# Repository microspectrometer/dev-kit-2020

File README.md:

Welcome to Chromation's dev-kit resources!

# How to read this

If you are reading this online at Chromation's microspectrometer
GitHub repository, please go to Chromation's GitHub pages site:

https://microspectrometer.github.io/dev-kit-2020/

It's the same docs, but the above link lets your browser run the
HTML portion of the docs.

# A quick overview

This is the **Chromation Spectrometer Development Kit**
(dev-kit):

![dev-kit with usb-bridge stacked on
top](img/photo/dev-kit-with-usb-bridge-not-rotated.jpg)

Use this kit to develop applications with the Chromation
spectrometer chip `CUVV-45-1-1-1-SMT`:

The spectrometer chip has the standard interface for a 1D CMOS
image sensor:

- analog video out
- digital I/O to control exposure and pixel readout

The dev-kit mounts the spectrometer chip on a breakout board with
an 8-pin ZIF connector for connection to other circuit boards
with a flex cable:

The dev-kit can be simply be plugged in and used as shipped, or
taken apart to access lower-level interfaces. This illustration
shows the dev-kit's hardware seams:

# Table of Contents

- [Getting started](getting-started.md)
- [Repository contents and license](repo-contents.md)
- [CUVV-45-1-1-1-SMT datasheet](hardware/design/CUVV-45-1-1-1-SMT/CUVV-45-1-1-1-SMT_technical-note-1.0.pdf)
- [Doxygen firmware documentation](firmware/doxygen/html/index.html)

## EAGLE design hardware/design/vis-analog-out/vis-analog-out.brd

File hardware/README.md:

# Chromation dev-kit design and manufacturing files

## Complete file list

The complete list of files is below. Some files listed below are
not publicly available yet but will become available soon.

```
hardware
├── manufacture
│   ├── usb-bridge
│   │   ├── DrillFiles
│   │   ├── Gerber
│   │   └── usb-bridge-xyrs-bom.csv
│   ├── vis-analog-out
│   │   ├── DrillFiles
│   │   ├── Gerber
│   │   └── vis-analog-out-xyrs-bom.csv
│   └── vis-spi-out
│       ├── DrillFiles
│       ├── Gerber
│       └── vis-spi-out-xyrs-bom.csv
└── design
    ├── CUVV-45-1-1-1-SMT
    │   ├── LICENSE.md
    │   ├── CUVV-45-1-1-1-SMT_technical-note-1.0.pdf
    │   └── step
    │       ├── CUVV-45-1-1-1-SMT v1.f3d
    │       └── CUVV-45-1-1-1-SMT v1.step
    ├── pdf
    │   ├── usb-bridge.pdf
    │   ├── vis-analog-out.pdf
    │   └── vis-spi-out.pdf
    ├── lbr (EAGLE library components)
    ├── usb-bridge
    │   ├── datasheets
    │   ├── eagle.epf
    │   ├── hardware-design.md
    │   ├── usb-bridge.brd
    │   ├── usb-bridge.sch
    │   └── usb-bridge-xyrs-bom.csv
    ├── vis-analog-out
    │   ├── CAM
    │   ├── eagle.epf
    │   ├── hardware-design.md
    │   ├── step
    │   ├── vis-analog-out.brd
    │   ├── vis-analog-out.sch
    │   └── vis-analog-out-xyrs-bom.csv
    └── vis-spi-out
        ├── CAM
        ├── datasheets
        ├── eagle.epf
        ├── hardware-design.md
        ├── vis-spi-out.brd
        ├── vis-spi-out.sch
        └── vis-spi-out-xyrs-bom.csv
```

## CAD files

### Spectrometer chip package CAD files and documentation

This documentation is intended for PCB layout and opto-mechanical
alignment.

*Chromation does not provide design and manufacturing files for
the internal design of the spectrometer chip itself.*

#### Chip package render

The chip package should look like this after importing into 3D
CAD software:

![CUVV-45-1-1-1-SMT
render](design/CUVV-45-1-1-1-SMT/render/CUVV-45-1-1-1-SMT.png)

#### 3D CAD files

```
hardware
└── design
    └── CUVV-45-1-1-1-SMT
       └── step
            ├── CUVV-45-1-1-1-SMT v1.f3d
            └── CUVV-45-1-1-1-SMT v1.step
```

The chip package is designed in Fusion360.

- if you use Fusion360, import the `.f3d` file
- if you use different 3D CAD software, import the `.step` file
- if you do not have 3D CAD software, you can still view the part
  and measure features [using this link](https://a360.co/2CVHmGy)

See
`hardware/design/CUVV-45-1-1-1-SMT/CUVV-45-1-1-1-SMT_technical-note-1.0.pdf` for additional information about the spectrometer chip.

### PCB CAD files and documentation

#### vis-analog-out

![vis-analog-out
render](design/vis-analog-out/render/pcb.png)

#### vis-spi-out

![vis-spi-out
render](design/vis-spi-out/render/pcb.png)

#### usb-bridge

![usb-bridge
render](design/usb-bridge/render/pcb.png)

#### EAGLE

The PCBs (printed circuit boards) are designed in EAGLE.

The EAGLE files are in the `hardware/design` folder. The
following files are available now, additional design files are
coming soon.

EAGLE library components:

```
└── lbr
    ├── eagle-pkg-artwork.md
    ├── 0603.lbr (resistors and capacitors)
    ├── YAGEO-0603.lbr (resistors)
    ├── ADC.lbr
    ├── ATMEGA328.lbr
    ├── BICOLOR-LED.lbr (red/green led)
    ├── Chromation.lbr
    │   ├── ADP3303_ (3.3V regulator)
    │   ├── APTD1608SYCK_ (power indicator LED)
    │   ├── FB_ (ferrite bead for USB back-emi filter)
    │   ├── LETTER_L (schematic sheet border)
    │   ├── MOUNTING-HOLE_ (#2-56 hole)
    │   └── OPA2364_ (dual op-amp)
    ├── CRYSTAL.lbr (MCU 10MHz oscillator)
    ├── DOWEL-PIN.lbr (2.5mm pin to quick-mount usb-bridge PCB)
    ├── DPDT.lbr (double-pole slide switch)
    ├── FT221X.lbr (USB Bridge IC)
    ├── HEADER-PIN.lbr (16-pin b2b male)
    ├── HEADER-SOCKET.lbr (16-pin b2b female, 2-pin i2c female)
    ├── ISP.lbr (in-system-programming shrouded header)
    ├── MICRO-USB.lbr (usb connector)
    ├── POT.lbr (trimpot for dark-correction)
    ├── PUSH-BUTTON.lbr (reset button, not always populated)
    ├── R-ARRAY.lbr (resistor arrays for current-limiting)
    ├── SPDT.lbr (single-pole slide switch)
    ├── TEST-POINT.lbr
    ├── USB-BRIDGE.lbr (footprint of usb-bridge PCB)
    ├── VIS-PKG.lbr (Chromation Spectrometer chip)
    ├── VREF.lbr (ADC voltage reference)
    └── ZIF.lbr (FFC connector)
```

PCB design files:

```
├── usb-bridge
│   ├── render
│   │   └── pcb.png
│   ├── datasheets/
│   ├── eagle.epf
│   ├── usb-bridge.brd
│   ├── usb-bridge.sch
│   └── usb-bridge-xyrs-bom.csv
├── vis-analog-out
│   ├── render
│   │   └── pcb.png
│   ├── hardware-design.md
│   ├── eagle.epf
│   ├── vis-analog-out.brd
│   ├── vis-analog-out.sch
│   └── vis-analog-out-xyrs-bom.csv
└── vis-spi-out
    ├── render
    │   └── pcb.png
    ├── datasheets/
    ├── eagle.epf
    ├── vis-spi-out.brd
    ├── vis-spi-out.sch
    └── vis-spi-out-xyrs-bom.csv
```

- if you have EAGLE, simply open the project (this reads the
  `.epf` file to determine which files to open)
- if you do not have EAGLE but are able to import EAGLE files:
    - the schematic is the `.sch`
    - the board is the `.brd`
    - the BOM-and-pick-and-place is the `-xyrs-bom.csv`
    - the library components for all three boards are the `.lbr`
      files in the `hardware/design/lbr` folder
- if you do not have EAGLE and are unable to import EAGLE files:
    - PDFs of the circuit schematics are in `hardware/design/pdf`

- [ ] hardware-design.md is electronics design calculations and
  related documentation
    - [vis-analog-out hardware-design.md](design/vis-analog-out/hardware-design.md)
    - [vis-spi-out hardware-design.md](design/vis-spi-out/hardware-design.md)
    - [usb-bridge hardware-design.md](design/usb-bridge/hardware-design.md)
- [ ] The manufacturing files (Gerbers and Drill) are in the
  `hardware/manufacture` folder.

- view the Gerbers with a Gerber viewer such as `gerbv`
- the PCBs are 4-layer
- `gerbv` screenshots of each layer-view
  (top/bottom/inner1/inner2) are in `hardware/manufacture/img`

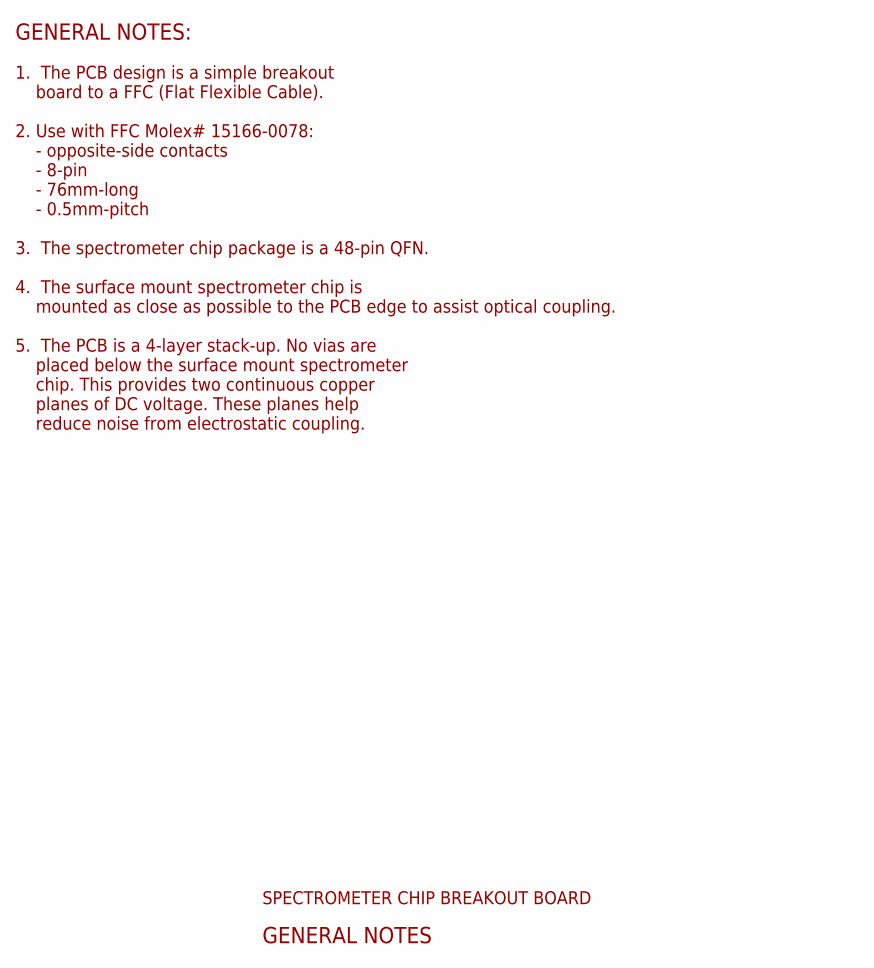
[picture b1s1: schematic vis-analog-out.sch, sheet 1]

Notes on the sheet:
SPECTROMETER CHIP BREAKOUT BOARD
GENERAL NOTES
1. The PCB design is a simple breakout board to a FFC (Flat Flexible Cable). 2. Use with FFC Molex# 15166-0078: - opposite-side contacts - 8-pin - 76mm-long - 0.5mm-pitch 3. The spectrometer chip package is a 48-pin QFN. 4. The surface mount spectrometer chip is mounted as close as possible to the 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
GENERAL NOTES:

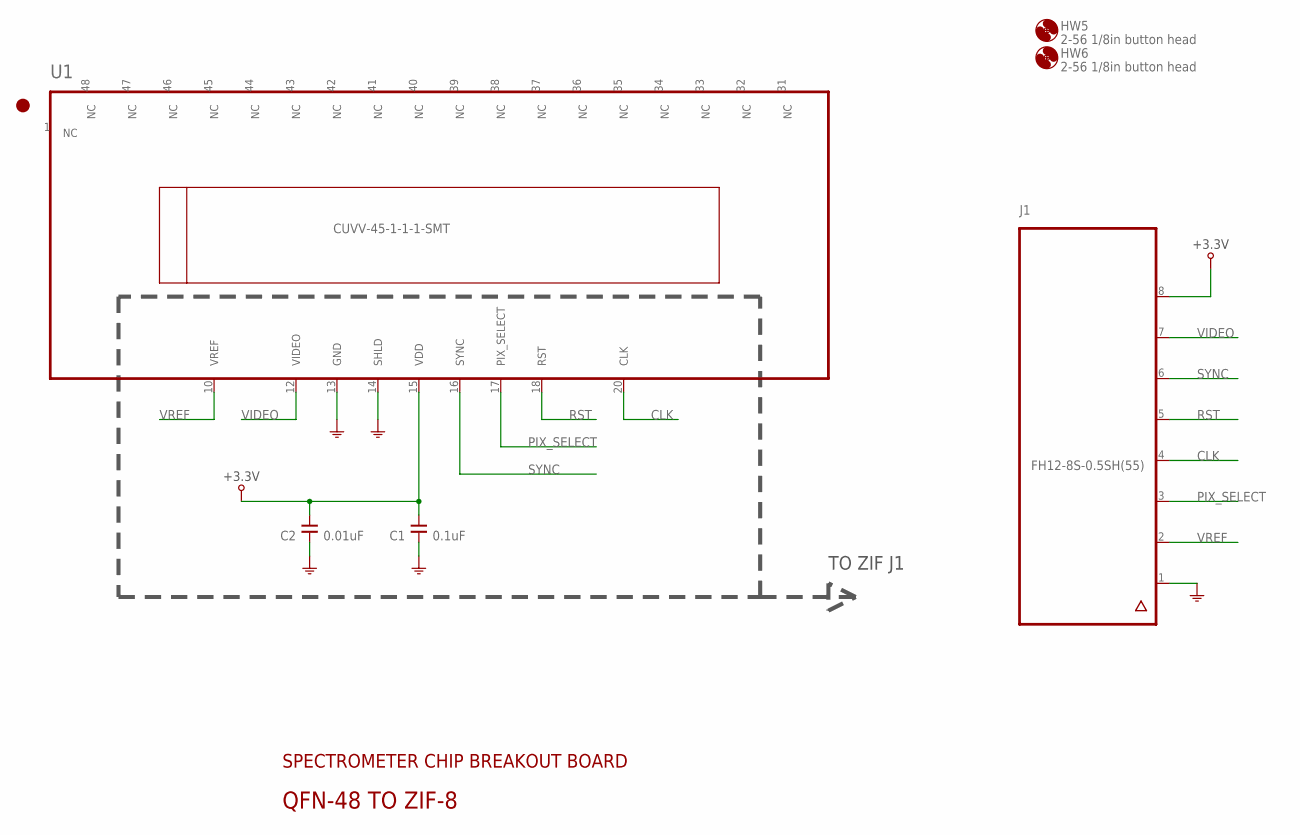
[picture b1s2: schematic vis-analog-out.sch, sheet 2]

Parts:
C1: 0.1uF; 0603; MANUF_PNUM CGA3E2X7R1H104K080AA
C2: 0.01uF; 0603; MANUF_PNUM C0603C103K5RACTU
HW5, HW6: 2-56 1/8in button head; MCMASTER_92949A081; MANUF_PNUM --
J1: FH12-8S-0.5SH(55); FH12-8S-0.5SH; MANUF_PNUM FH12-8S-0.5SH(55)
U1: CUVV-45-1-1-1-SMT; VIS-PKG; MANUF_PNUM CUVV-45-1-1-1-SMT

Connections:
+3.3V: C1.1, C2.1, J1.8, U1.15 (VDD)
CLK: J1.4, U1.20 (CLK)
GND: C1.2, C2.2, J1.1, U1.13 (GND), U1.14 (SHLD)
PIX_SELECT: J1.3, U1.17 (PIX_SELECT)
RST: J1.5, U1.18 (RST)
SYNC: J1.6, U1.16 (SYNC)
VIDEO: J1.7, U1.12 (VIDEO)
VREF: J1.2, U1.10 (VREF)

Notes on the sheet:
SPECTROMETER CHIP BREAKOUT BOARD
QFN-48 TO ZIF-8
TO ZIF J1

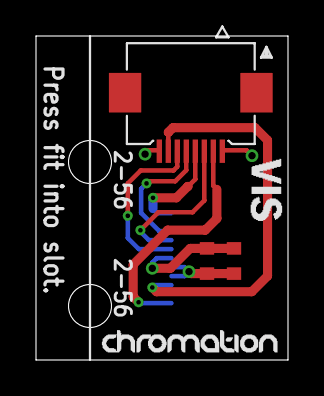
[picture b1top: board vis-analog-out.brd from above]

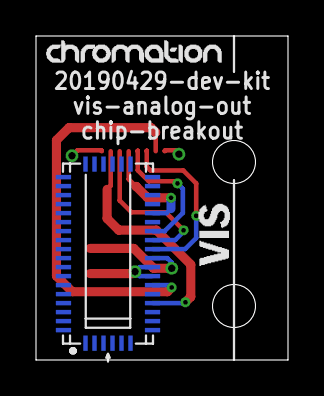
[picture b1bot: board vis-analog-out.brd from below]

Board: 4 copper layers, 14.0 x 18.0 mm, 6 parts (3 on the bottom side), 8 nets.

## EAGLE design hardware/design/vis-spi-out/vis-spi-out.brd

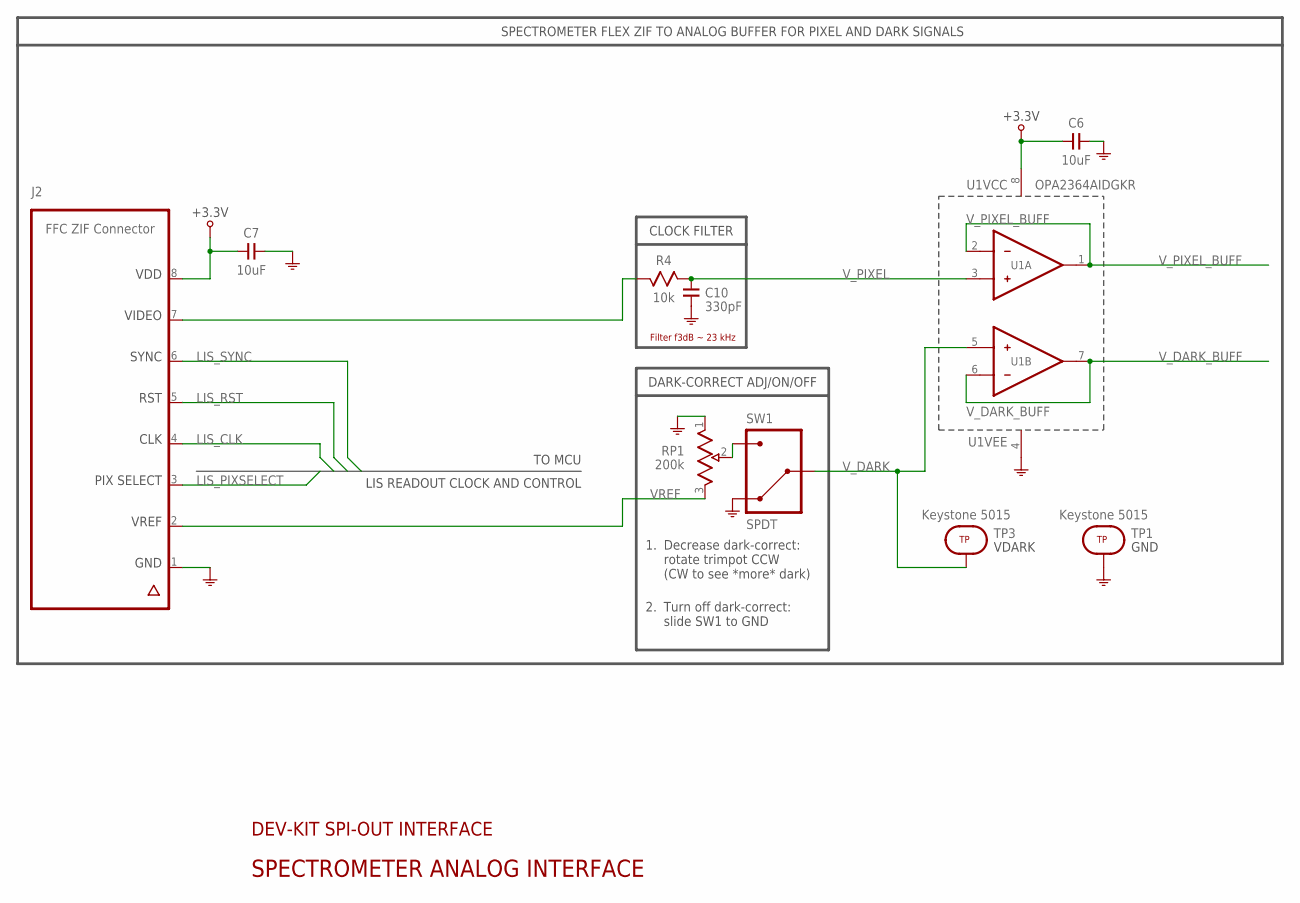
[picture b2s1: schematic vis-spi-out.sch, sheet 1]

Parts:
C6, C7: 10uF; 0603; MANUF_PNUM GRM188R6YA106MA73D
C10: 330pF; 0603; MANUF_PNUM GCM1885C2A331FA16D
J2: FFC ZIF Connector; FH12-8S-0.5SH; MANUF_PNUM FH12-8S-0.5SH(55)
R4: 10k; 0603; MANUF_PNUM RC0603FR-0710KL
RP1: 200k; TC3XX-2-204E; MANUF_PNUM TC33X-2-204E
SW1: SPDT; JS102011JCQN; MANUF_PNUM JS102011JCQN
TP1, TP3: Keystone 5015; SMT-TEST-POINT-5015; MANUF_PNUM 5015
U1: OPA2364AIDGKR; DGK; MANUF_PNUM OPA2364AIDGKR

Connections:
+3.3V: C6.2, C7.2, J2.8, U1.8 (VCC); also elsewhere on the board
GND: C6.1, C7.1, C10.2, J2.1, RP1.1 (CCW), SW1.3, TP1.1, U1.4 (VEE); also elsewhere on the board
LIS_CLK: J2.4; also elsewhere on the board
LIS_PIXSELECT: J2.3; also elsewhere on the board
LIS_RST: J2.5; also elsewhere on the board
LIS_SYNC: J2.6; also elsewhere on the board
VIDEO: J2.7, R4.1
VREF: J2.2, RP1.3 (CW)
V_DARK: SW1.2, TP3.1, U1.5 (IN+)
V_DARK_BUFF: U1.6 (IN-), U1.7 (OUT); also elsewhere on the board
V_PIXEL: C10.1, R4.2, U1.3 (IN+)
V_PIXEL_BUFF: U1.1 (OUT), U1.2 (IN-); also elsewhere on the board
WIPER: RP1.2 (WIPER), SW1.1

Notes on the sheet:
VDD
GND
VIDEO
VREF
SYNC
PIX SELECT
RST
CLK
CLOCK FILTER
LIS READOUT CLOCK AND CONTROL
SPECTROMETER FLEX ZIF TO ANALOG BUFFER FOR PIXEL AND DARK SIGNALS
TO MCU
Filter f3dB ~ 23 kHz
DARK-CORRECT ADJ/ON/OFF
Decrease dark-correct: rotate trimpot CCW (CW to see *more* dark)
Turn off dark-correct: slide SW1 to GND
DEV-KIT SPI-OUT INTERFACE
SPECTROMETER ANALOG INTERFACE

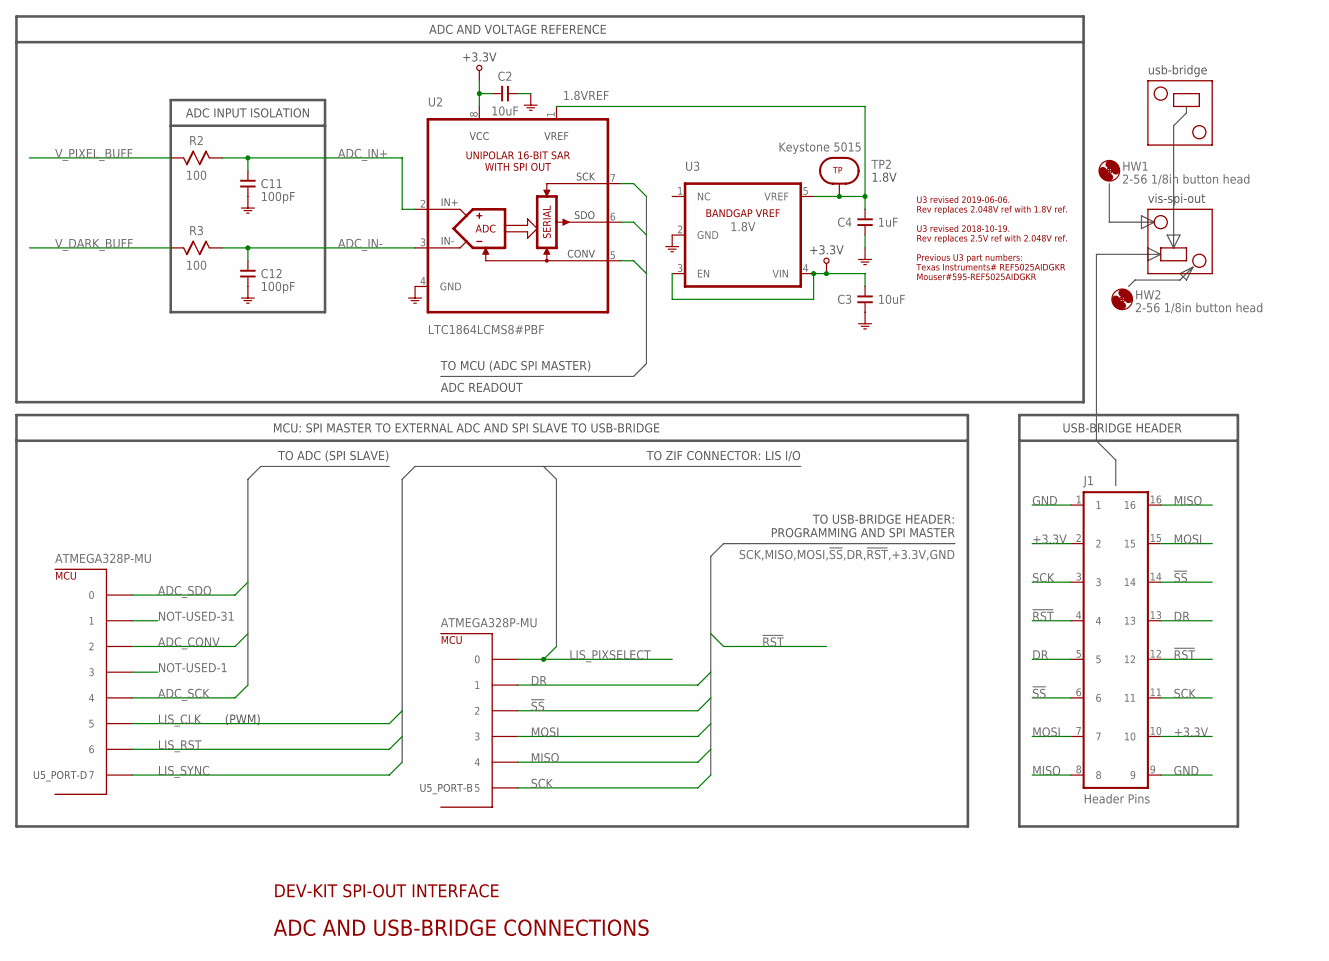
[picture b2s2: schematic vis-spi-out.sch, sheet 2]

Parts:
C2, C3: 10uF; 0603; MANUF_PNUM GRM188R6YA106MA73D
C4: 1uF; 0603; MANUF_PNUM CC0603KRX5R8BB105
C11, C12: 100pF; 0603; MANUF_PNUM GCM1885C2A101FA16D
HW1, HW2: 2-56 1/8in button head; MCMASTER_92949A081; MANUF_PNUM --
J1: Header Pins; TSM-108-01-S-DV; MANUF_PNUM TSM-108-01-S-DV-P-TR
R2, R3: 100; 0603; MANUF_PNUM RC0603FR-07100RL
ROTATED-USB-BRIDGE-PCB: USB-BRIDGE_FOOTPRINT-AND-USB-REF; OUTLINE-HEADER-MICROUSB
TP2: Keystone 5015; SMT-TEST-POINT-5015; MANUF_PNUM 5015
U2: LTC1864LCMS8#PBF; LTC1864LCMS8; MANUF_PNUM LTC1864LCMS8#PBF
U3: 1.8V; SOT23; MANUF_PNUM LM4132AMF-1.8/NOPB
U5: ATMEGA328P-MU; QFN-32_ATMEL; MANUF_PNUM ATMEGA328P-MUR
USB-BRDIGE-PCB: USB-BRIDGE_FOOTPRINT-AND-USB-REF; OUTLINE-HEADER-MICROUSB

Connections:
1.8VREF: C4.2, TP2.1, U2.1 (VREF), U3.5 (VREF)
!RST!: J1.4, J1.12; also elsewhere on the board
!SS!: J1.6, J1.14, U5.14 (2), U5.14F (2)
+3.3V: C2.2, C3.1, J1.2, J1.10, U2.8 (VCC), U3.3 (EN), U3.4 (VIN); also elsewhere on the board
ADC_CONV: U2.5 (CONV), U5.32 (2), U5.32F (2)
ADC_IN+: C11.1, R2.2, U2.2 (IN+)
ADC_IN-: C12.1, R3.2, U2.3 (IN-)
ADC_SCK: U2.7 (SCK), U5.2 (4), U5.2F (4)
ADC_SDO: U2.6 (SDO), U5.30 (0), U5.30F (0)
DR: J1.5, J1.13, U5.13 (1), U5.13F (1)
GND: C2.1, C3.2, C4.1, C11.2, C12.2, J1.1, J1.9, U2.4 (GND), U3.2 (GND); also elsewhere on the board
LIS_CLK: U5.9 (5), U5.9F (5); also elsewhere on the board
LIS_PIXSELECT: U5.12 (0), U5.12F (0); also elsewhere on the board
LIS_RST: U5.10 (6), U5.10F (6); also elsewhere on the board
LIS_SYNC: U5.11 (7), U5.11F (7); also elsewhere on the board
MISO: J1.8, J1.16, U5.16 (4), U5.16F (4)
MOSI: J1.7, J1.15, U5.15 (3), U5.15F (3)
NOT-USED-1: U5.1 (3), U5.1F (3)
NOT-USED-31: U5.31 (1), U5.31F (1)
SCK: J1.3, J1.11, U5.17 (5), U5.17F (5)
V_DARK_BUFF: R3.1; also elsewhere on the board
V_PIXEL_BUFF: R2.1; also elsewhere on the board

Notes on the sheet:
DEV-KIT SPI-OUT INTERFACE
ADC AND USB-BRIDGE CONNECTIONS
ADC INPUT ISOLATION
ADC READOUT
TO MCU (ADC SPI MASTER)
U3 revised 2019-06-06. Rev replaces 2.048V ref with 1.8V ref. U3 revised 2018-10-19. Rev replaces 2.5V ref with 2.048V ref. Previous U3 part numbers: Texas Instruments# REF5025AIDGKR Mouser#595-REF5025AIDGKR
ADC AND VOLTAGE REFERENCE
TO USB-BRIDGE HEADER: PROGRAMMING AND SPI MASTER
TO ZIF CONNECTOR: LIS I/O
(PWM)
TO ADC (SPI SLAVE)
MCU: SPI MASTER TO EXTERNAL ADC AND SPI SLAVE TO USB-BRIDGE
usb-bridge
vis-spi-out
USB-BRIDGE HEADER

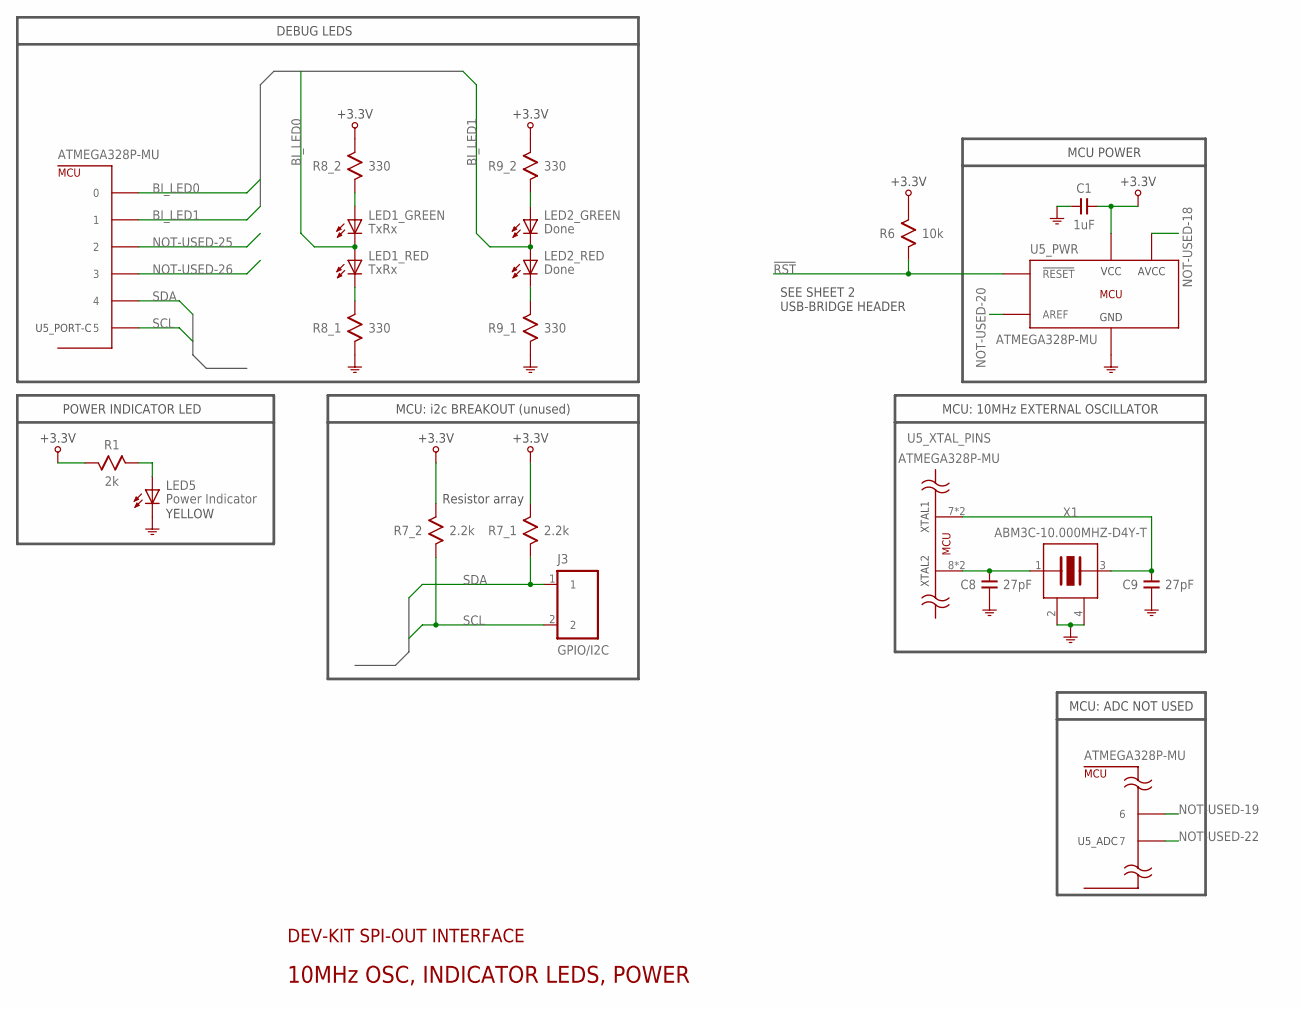
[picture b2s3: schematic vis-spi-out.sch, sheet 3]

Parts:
C1: 1uF; 0603; MANUF_PNUM CC0603KRX5R8BB105
C8, C9: 27pF; 0603; MANUF_PNUM GRM1885C1H270FA01J
J3: GPIO/I2C; SSM-102-S-SV; MANUF_PNUM SSM-102-S-SV-K-TR
LED1: TxRx; HSMF-C16X; MANUF_PNUM HSMF-C165
LED2: Done; HSMF-C16X; MANUF_PNUM HSMF-C165
LED5: Power Indicator; LED-0603-KINGBRIGHT; MANUF_PNUM APTD1608SYCK
R1: 2k; 0603; MANUF_PNUM RC0603FR-072KL
R6: 10k; 0603; MANUF_PNUM RC0603FR-0710KL
R7: 2.2k; 742C043; MANUF_PNUM 742C043222JP
R8, R9: 330; 742C043; MANUF_PNUM 742C043331JP
U5: ATMEGA328P-MU; QFN-32_ATMEL; MANUF_PNUM ATMEGA328P-MUR
X1: ABM3C-10.000MHZ-D4Y-T; CRYSTAL; MANUF_PNUM ABM3C-10.000MHZ-D4Y-T

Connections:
!RST!: R6.1, U5.29 (!RESET!), U5.29F (!RESET!); also elsewhere on the board
+3.3V: C1.2, R1.1, R6.2, R7.1, R7.3 (1), R8.3 (1), R9.3 (1), U5.4 (VCC), U5.4F (VCC), U5.6 (VCC), U5.6F (VCC); also elsewhere on the board
BI_LED0: LED1.2 (A), LED1.3 (C), U5.23 (0), U5.23F (0)
BI_LED0_GREEN: LED1.1 (A), R8.4 (2)
BI_LED0_RED: LED1.4 (C), R8.1
BI_LED1: LED2.2 (A), LED2.3 (C), U5.24 (1), U5.24F (1)
BI_LED1_GREEN: LED2.1 (A), R9.4 (2)
BI_LED1_RED: LED2.4 (C), R9.1
GND: C1.1, C8.2, C9.2, LED5.2 (C), R8.2, R9.2, U5.3 (GND), U5.3F (GND), U5.5 (GND), U5.5F (GND), U5.21 (GND), U5.21F (GND), U5.THERMAL (GND), X1.2 (GND), X1.4 (GND); also elsewhere on the board
unnamed: LED5.1 (A), R1.2
NOT-USED-18: U5.18 (AVCC), U5.18F (AVCC)
NOT-USED-19: U5.19 (6), U5.19F (6)
NOT-USED-20: U5.20 (AREF), U5.20F (AREF)
NOT-USED-22: U5.22 (7), U5.22F (7)
NOT-USED-25: U5.25 (2), U5.25F (2)
NOT-USED-26: U5.26 (3), U5.26F (3)
SCL: J3.2, R7.4 (2), U5.28 (5), U5.28F (5)
SDA: J3.1, R7.2, U5.27 (4), U5.27F (4)
XTAL1: C9.1, U5.7 (XTAL1), U5.7F (XTAL1), X1.3
XTAL2: C8.1, U5.8 (XTAL2), U5.8F (XTAL2), X1.1

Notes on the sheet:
DEV-KIT SPI-OUT INTERFACE
10MHz OSC, INDICATOR LEDS, POWER
DEBUG LEDS
POWER INDICATOR LED
YELLOW
MCU: ADC NOT USED
MCU POWER
MCU: 10MHz EXTERNAL OSCILLATOR
Resistor array
MCU: i2c BREAKOUT (unused)
SEE SHEET 2 USB-BRIDGE HEADER

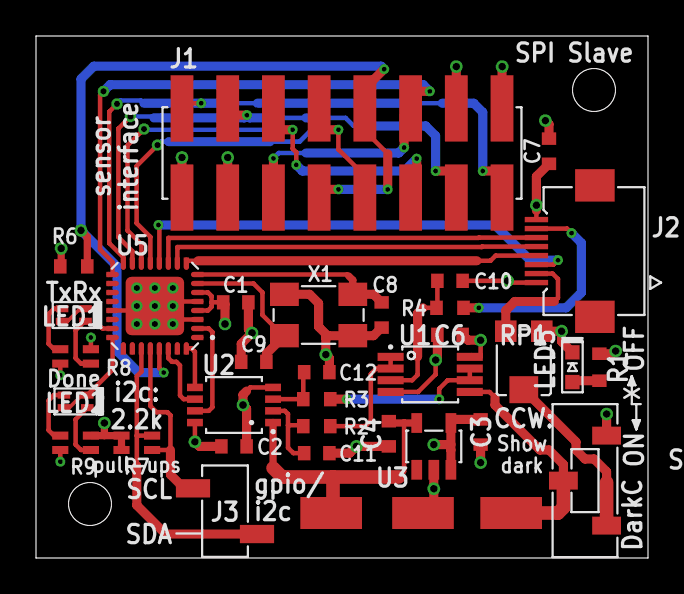
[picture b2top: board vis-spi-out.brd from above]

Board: 4 copper layers, 34.0 x 29.0 mm, 39 parts (0 on the bottom side), 44 nets.

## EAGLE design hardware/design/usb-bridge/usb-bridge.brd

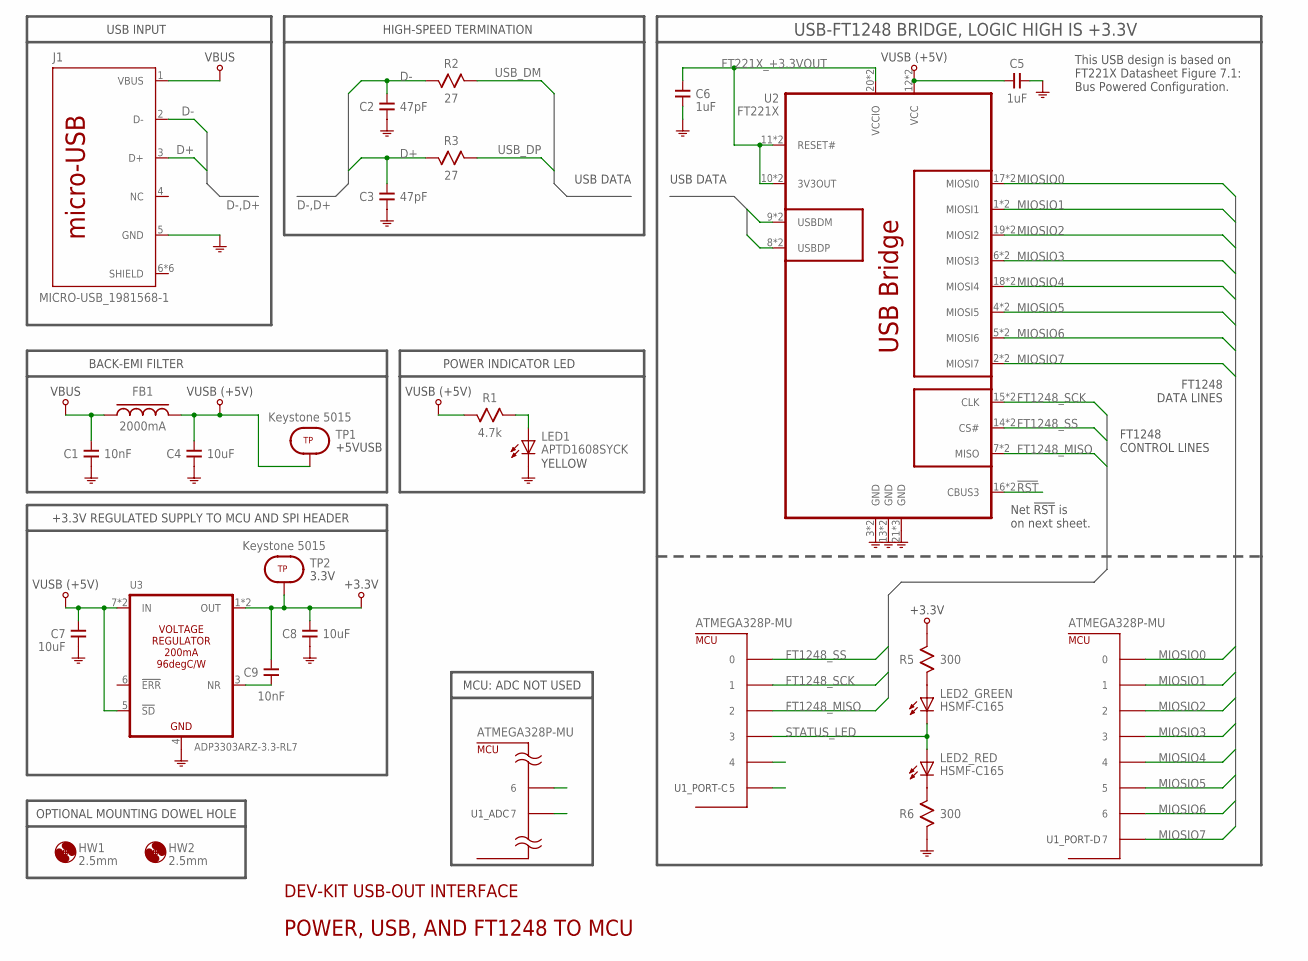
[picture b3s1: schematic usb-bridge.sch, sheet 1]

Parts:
C1, C9: 10nF; 0603; MANUF_PNUM GRM1885C1H103JA01D
C2, C3: 47pF; 0603; MANUF_PNUM GCM1885C2A470FA16D
C4, C7, C8: 10uF; 0603; MANUF_PNUM GRM188R6YA106MA73D
C5, C6: 1uF; 0603; MANUF_PNUM CC0603KRX5R8BB105
FB1: 2000mA; FB-LAIRD-0603; MANUF_PNUM MI0603L301R-10
HW1, HW2: 2.5mm; MCMASTER-93600A265
J1: MICRO-USB_1981568-1; TE_1981568-1; MANUF_PNUM 1981568-1
LED1: APTD1608SYCK; LED-0603-KINGBRIGHT; MANUF_PNUM APTD1608SYCK
LED2: HSMF-C165; HSMF-C16X; MANUF_PNUM HSMF-C165
R1: 4.7k; 0603; MANUF_PNUM RC0603FR-074K7L
R2, R3: 27; 0603; MANUF_PNUM RC0603FR-0727RL
R5, R6: 300; 0603; MANUF_PNUM RC0603FR-07300RL
TP1, TP2: Keystone 5015; SMT-TEST-POINT-5015; MANUF_PNUM 5015
U1: ATMEGA328P-MU; QFN-32_ATMEL; MANUF_PNUM ATMEGA328P-MUR
U2: FT221X; QFN-20; MANUF_PNUM FT221XQ-R
U3: ADP3303ARZ-3.3-RL7; SOIC-8_AD; MANUF_PNUM ADP3303ARZ-3.3-RL7

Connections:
!RST!: U2.16 (CBUS3), U2._16 (CBUS3); also elsewhere on the board
+3.3V: C8.1, C9.1, R5.1, TP2.1, U3.1 (OUT), U3.2 (OUT); also elsewhere on the board
+5VUSB: C4.1, C5.1, C7.1, FB1.2, R1.1, TP1.1, U2.12 (VCC), U2._12 (VCC), U3.5 (!SD!), U3.7 (IN), U3.8 (IN)
D+: C3.1, J1.3 (D+), R3.1
D-: C2.1, J1.2 (D-), R2.1
FT221X_+3.3VOUT: C6.1, U2.10 (3V3OUT), U2.11 (RESET#), U2.20 (VCCIO), U2._10 (3V3OUT), U2._11 (RESET#), U2._20 (VCCIO)
FT1248_MISO: U1.25 (2), U1.25F (2), U2.7 (MISO), U2._7 (MISO)
FT1248_SCK: U1.24 (1), U1.24F (1), U2.15 (CLK), U2._15 (CLK)
FT1248_SS: U1.23 (0), U1.23F (0), U2.14 (CS#), U2._14 (CS#)
GND: C1.2, C2.2, C3.2, C4.2, C5.2, C6.2, C7.2, C8.2, J1.5 (GND), LED1.2 (C), R6.2, U2.3 (GND), U2.13 (GND), U2.21 (GND), U2.21A (GND), U2.21B (GND), U2._3 (GND), U2._13 (GND), U3.4 (GND); also elsewhere on the board
MIOSIO0: U1.30 (0), U1.30F (0), U2.17 (MIOSI0), U2._17 (MIOSI0)
MIOSIO1: U1.31 (1), U1.31F (1), U2.1 (MIOSI1), U2._1 (MIOSI1)
MIOSIO2: U1.32 (2), U1.32F (2), U2.19 (MIOSI2), U2._19 (MIOSI2)
MIOSIO3: U1.1 (3), U1.1F (3), U2.6 (MIOSI3), U2._6 (MIOSI3)
MIOSIO4: U1.2 (4), U1.2F (4), U2.18 (MIOSI4), U2._18 (MIOSI4)
MIOSIO5: U1.9 (5), U1.9F (5), U2.4 (MIOSI5), U2._4 (MIOSI5)
MIOSIO6: U1.10 (6), U1.10F (6), U2.5 (MIOSI6), U2._5 (MIOSI6)
MIOSIO7: U1.11 (7), U1.11F (7), U2.2 (MIOSI7), U2._2 (MIOSI7)
unnamed: LED2.4 (C), R6.1
unnamed: LED2.1 (A), R5.2
unnamed: LED1.1 (A), R1.2
NOISE_REDUCTION: C9.2, U3.3 (NR)
NOT-USED-19: U1.19 (6), U1.19F (6)
NOT-USED-22: U1.22 (7), U1.22F (7)
NOT-USED-27: U1.27 (4), U1.27F (4)
NOT-USED-28: U1.28 (5), U1.28F (5)
STATUS_LED: LED2.2 (A), LED2.3 (C), U1.26 (3), U1.26F (3)
USB_DM: R2.2, U2.9 (USBDM), U2._9 (USBDM)
USB_DP: R3.2, U2.8 (USBDP), U2._8 (USBDP)
VBUS: C1.1, FB1.1, J1.1 (VBUS)

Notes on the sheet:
USB INPUT
BACK-EMI FILTER
HIGH-SPEED TERMINATION
USB-FT1248 BRIDGE, LOGIC HIGH IS +3.3V
FT1248 DATA LINES
FT1248 CONTROL LINES
USB DATA
This USB design is based on FT221X Datasheet Figure 7.1: Bus Powered Configuration.
POWER INDICATOR LED
YELLOW
OPTIONAL MOUNTING DOWEL HOLE
+3.3V REGULATED SUPPLY TO MCU AND SPI HEADER
Net !RST! is on next sheet.
DEV-KIT USB-OUT INTERFACE
POWER, USB, AND FT1248 TO MCU
MCU: ADC NOT USED

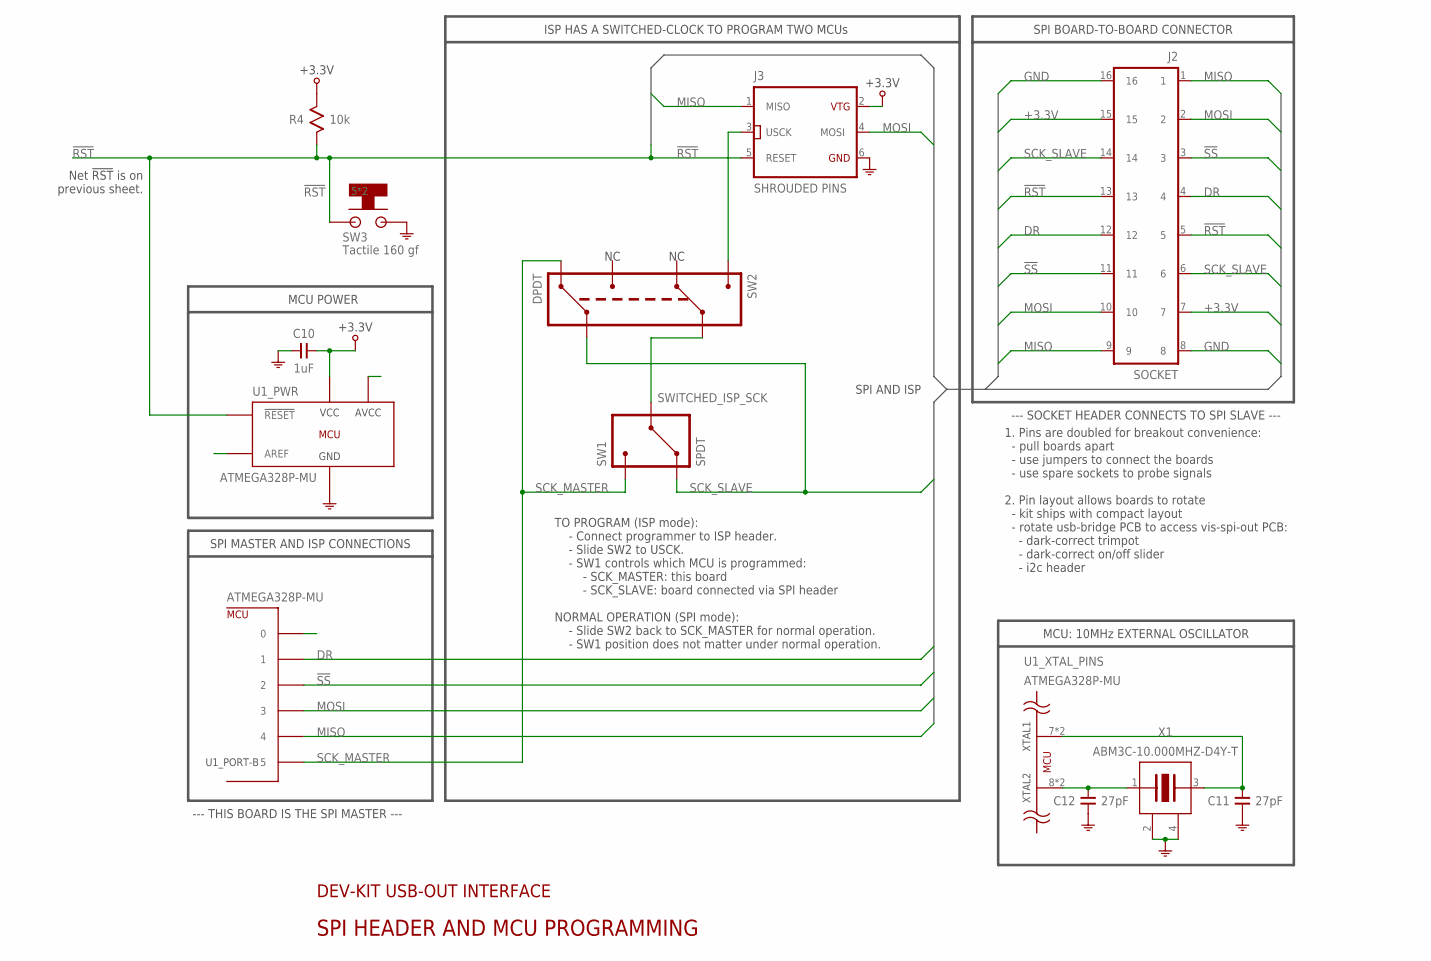
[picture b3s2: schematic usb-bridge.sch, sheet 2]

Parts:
C10: 1uF; 0603; MANUF_PNUM CC0603KRX5R8BB105
C11, C12: 27pF; 0603; MANUF_PNUM GRM1885C1H270FA01J
J2: SOCKET; SSM-108-L-DV; MANUF_PNUM SSM-108-L-DV-K-TR
J3: SHROUDED PINS; N2506-6V0C; MANUF_PNUM N2506-6V0C-RB-WD
R4: 10k; 0603; MANUF_PNUM RC0603FR-0710KL
SW1: SPDT; JS102011JCQN; MANUF_PNUM JS102011JCQN
SW2: DPDT; JS202011JCQN; MANUF_PNUM JS202011JCQN
SW3: Tactile 160 gf; MSLPT5252BL3MTR; MANUF_PNUM MSLPT5252BG3MTR
U1: ATMEGA328P-MU; QFN-32_ATMEL; MANUF_PNUM ATMEGA328P-MUR
X1: ABM3C-10.000MHZ-D4Y-T; CRYSTAL; MANUF_PNUM ABM3C-10.000MHZ-D4Y-T

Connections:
!RST!: J2.5, J2.13, J3.5 (RESET), R4.2, SW3.3 (3,4), SW3.4 (3,4), U1.29 (!RESET!), U1.29F (!RESET!); also elsewhere on the board
!SS!: J2.3, J2.11, U1.14 (2), U1.14F (2)
+3.3V: C10.2, J2.7, J2.15, J3.2 (VTTL), R4.1, U1.4 (VCC), U1.4F (VCC), U1.6 (VCC), U1.6F (VCC); also elsewhere on the board
DR: J2.4, J2.12, U1.13 (1), U1.13F (1)
GND: C10.1, C11.2, C12.2, J2.8, J2.16, J3.6 (GND), SW3.1 (1,2), SW3.2 (1,2), U1.3 (GND), U1.3F (GND), U1.5 (GND), U1.5F (GND), U1.21 (GND), U1.21F (GND), U1.THERMAL (GND), X1.2 (GND), X1.4 (GND); also elsewhere on the board
ISP_SCK: J3.3 (USCK), SW2.1
MISO: J2.1, J2.9, J3.1 (MISO), U1.16 (4), U1.16F (4)
MOSI: J2.2, J2.10, J3.4 (MOSI), U1.15 (3), U1.15F (3)
unnamed: C11.1, U1.7 (XTAL1), U1.7F (XTAL1), X1.3
unnamed: C12.1, U1.8 (XTAL2), U1.8F (XTAL2), X1.1
NOT-USED-12: U1.12 (0), U1.12F (0)
NOT-USED-18: U1.18 (AVCC), U1.18F (AVCC)
NOT-USED-20: U1.20 (AREF), U1.20F (AREF)
SCK_MASTER: SW1.1, SW2.6, U1.17 (5), U1.17F (5)
SCK_SLAVE: J2.6, J2.14, SW1.3, SW2.5
SWITCHED_ISP_SCK: SW1.2, SW2.2

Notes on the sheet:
SPI AND ISP
MCU: 10MHz EXTERNAL OSCILLATOR
DEV-KIT USB-OUT INTERFACE
SPI HEADER AND MCU PROGRAMMING
TO PROGRAM (ISP mode): - Connect programmer to ISP header. - Slide SW2 to USCK. - SW1 controls which MCU is programmed: - SCK_MASTER: this board - SCK_SLAVE: board connected via SPI header NORMAL OPERATION (SPI mode): - Slide SW2 back to SCK_MASTER for normal operation. - SW1 position does not matt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
Net !RST! is on previous sheet.
SPI BOARD-TO-BOARD CONNECTOR
MCU POWER
SPI MASTER AND ISP CONNECTIONS
ISP HAS A SWITCHED-CLOCK TO PROGRAM TWO MCUs
--- THIS BOARD IS THE SPI MASTER ---
--- SOCKET HEADER CONNECTS TO SPI SLAVE ---
1. Pins are doubled for breakout convenience: - pull boards apart - use jumpers to connect the boards - use spare sockets to probe signals 2. Pin layout allows boards to rotate - kit ships with compact layout - rotate usb-bridge PCB to access vis-spi-out PCB: - dark-correct trimpot - dark-correct o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

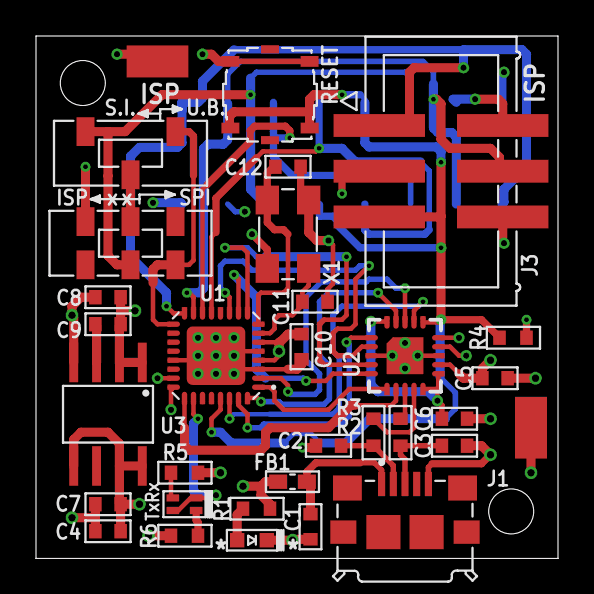
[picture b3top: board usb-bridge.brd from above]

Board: 4 copper layers, 29.0 x 29.0 mm, 35 parts (1 on the bottom side), 43 nets.

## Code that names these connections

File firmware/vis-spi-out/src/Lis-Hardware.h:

/** \file
 * Lis uses general purpose I/O pins and a PWM pin to communicate
 * with the Dynamax LIS-770i linear photodiode array.
 * */
#ifndef _LIS_HARDWARE_H
#define _LIS_HARDWARE_H
#include <stdint.h>
#include <avr/io.h> // includes iom328p.h for hardware i/o values
#include "Lis.h"
// ---Registers---
lis_ptr Lis_ddr1   = &DDRD;
lis_ptr Lis_port1  = &PORTD;
lis_ptr Lis_pin1   = &PIND;
lis_ptr Lis_ddr2   = &DDRB;
lis_ptr Lis_port2  = &PORTB;
lis_ptr Lis_TCCR0A = &TCCR0A; // PWM
lis_ptr Lis_TCCR0B = &TCCR0B; // PWM
lis_ptr Lis_TIFR0  = &TIFR0;  // PWM
lis_ptr Lis_OCR0A  = &OCR0A;  // PWM
lis_ptr Lis_OCR0B  = &OCR0B;  // PWM
// ---Pins---
lis_pin Lis_PixSelect = PB0;
lis_pin Lis_Clk       = PD5; // PWM
lis_pin Lis_Rst       = PD6;
lis_pin Lis_Sync      = PD7;
// ---Bits---
lis_bit Lis_WGM00  = WGM00;  // PWM
lis_bit Lis_WGM01  = WGM01;  // PWM
lis_bit Lis_WGM02  = WGM02;  // PWM
lis_bit Lis_CS00   = CS00;   // PWM
lis_bit Lis_CS01   = CS01;   // PWM
lis_bit Lis_CS02   = CS02;   // PWM
lis_bit Lis_COM0B0 = COM0B0; // PWM
lis_bit Lis_COM0B1 = COM0B1; // PWM
lis_bit Lis_OCF0A  = OCF0A;  // PWM
lis_bit Lis_OCF0B  = OCF0B;  // PWM
#endif // _LIS_HARDWARE_H
